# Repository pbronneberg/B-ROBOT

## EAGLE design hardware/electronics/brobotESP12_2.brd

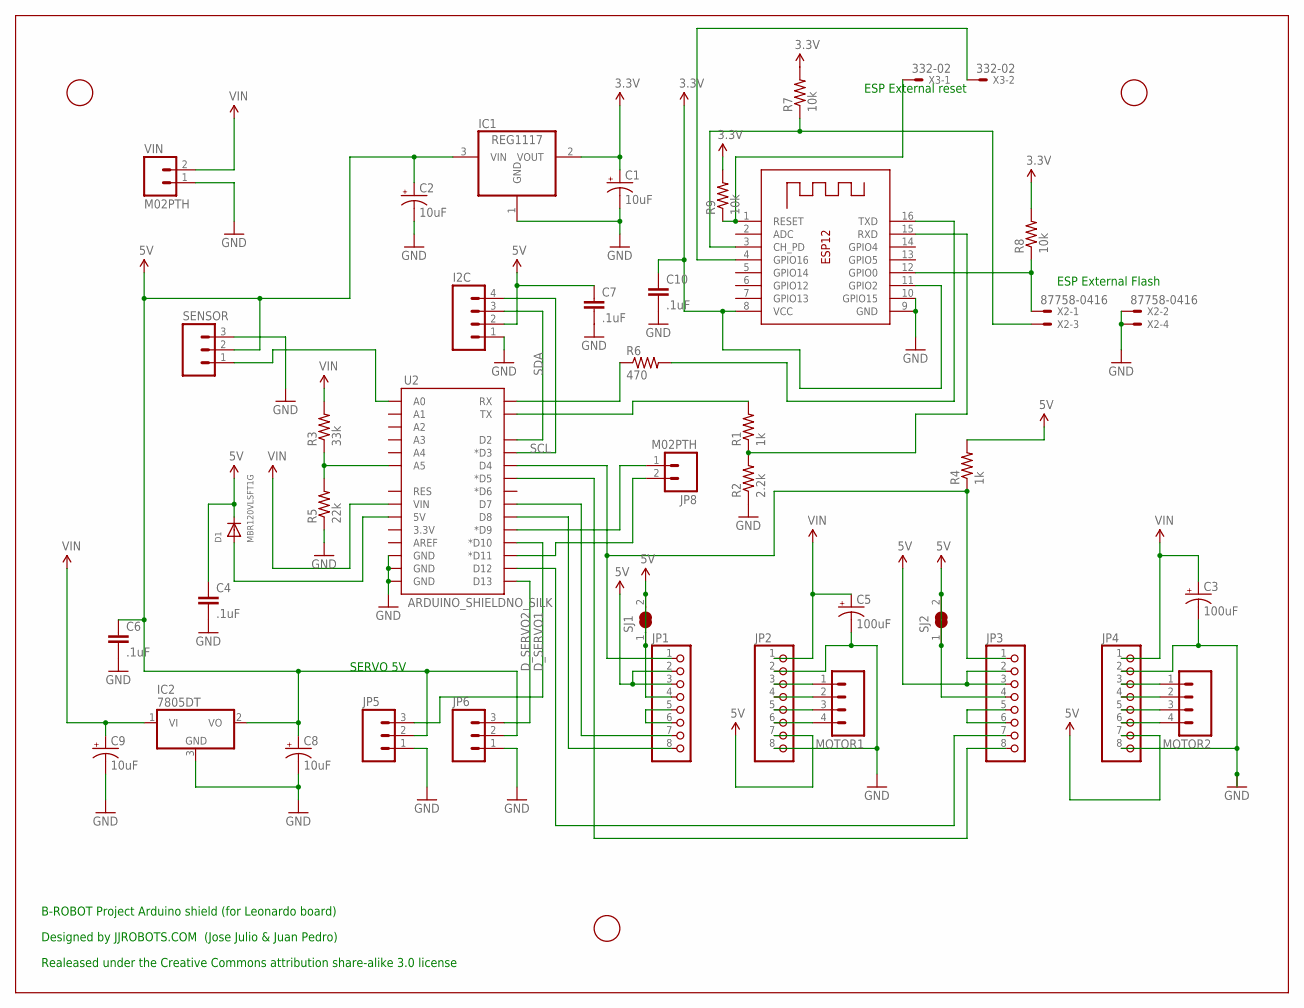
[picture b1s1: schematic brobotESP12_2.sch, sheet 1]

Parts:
C1, C2, C8, C9: 10uF; EIA3216
C3, C5: 100uF; PANASONIC_D
C4, C6, C7, C10: .1uF; 0402-CAP
D1: MBR120VLSFT1G; SOD-123
I2C: M04PTH; 1X04
IC1: REG1117; SOT223
IC2: 7805DT; TO252
JP1, JP2, JP3, JP4: PINHD-1X8; 1X08
JP5, JP6: M03PTH; 1X03
JP8: M02PTH; 1X02
MOTOR1, MOTOR2: M04PTH; 1X04
R1, R4: 1k; 0805
R2: 2.2k; 0805
R3: 33k; 0805
R5: 22k; 0805
R6: 470; 0805
R7, R8, R9: 10k; 0805
SENSOR: M03PTH; 1X03
SJ1, SJ2: SJW
U2: ARDUINO_SHIELDNO_SILK; DUEMILANOVE_VIAS
U$1, U$2, U$3: FIDUCIAL; FIDUCIAL_1MM
VIN: M02PTH; 1X02
X1: ESP-12
X2: 87758-0416
X3: 332-02

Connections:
3.3V: C1.A (+), C10.1, IC1.2 (VOUT), R7.2, R8.2, R9.2, X1.8 (VCC), X1.11 (GPIO2)
5V: C2.A (+), C4.1, C6.1, C7.1, C8.A (+), D1.C, I2C.2, IC1.3 (VIN), IC2.2 (VO), JP1.2, JP1.3, JP1.4, JP2.7, JP3.2, JP3.3, JP3.4, JP4.7, JP5.2, JP6.2, R4.2, SENSOR.2, SJ1.1, SJ1.2, SJ2.1, SJ2.2; also elsewhere on the board
A_SENSOR: SENSOR.1, U2.A0; also elsewhere on the board
A_VOLTAGE: R3.1, R5.2, U2.A5; also elsewhere on the board
D4: JP1.1, JP3.1, R4.1, U2.D4; also elsewhere on the board
D5: JP3.8, U2.D5 (*D5); also elsewhere on the board
D7: JP1.7, U2.D7; also elsewhere on the board
D8: JP1.8, U2.D8; also elsewhere on the board
D11: JP8.2, U2.D11 (*D11); also elsewhere on the board
D12: JP3.7, U2.D12; also elsewhere on the board
D_SERVO1: JP5.3, U2.D10 (*D10); also elsewhere on the board
D_SERVO2: JP6.3, U2.D13; also elsewhere on the board
GND: C1.C (-), C2.C (-), C3.-, C4.2, C5.-, C6.2, C7.2, C8.C (-), C9.C (-), C10.2, I2C.1, IC1.1 (GND), IC2.3 (GND), JP2.2, JP2.8, JP4.2, JP4.8, JP5.1, JP6.1, R2.1, R5.1, SENSOR.3, U2.GND@0 (GND), U2.GND@1 (GND), U2.GND@2 (GND), VIN.1, X1.9 (GND), X1.10 (GPIO15), X2.2, X2.4; also elsewhere on the board
unnamed: JP2.3, MOTOR1.1
unnamed: JP2.4, MOTOR1.2
unnamed: R6.2, X1.16 (TXD)
unnamed: R1.1, R2.2, X1.15 (RXD)
unnamed: JP2.5, MOTOR1.3
unnamed: JP2.6, MOTOR1.4
unnamed: JP4.3, MOTOR2.1
unnamed: JP4.4, MOTOR2.2
unnamed: JP4.5, MOTOR2.3
unnamed: JP1.5, JP1.6
unnamed: JP3.5, JP3.6
unnamed: JP4.6, MOTOR2.4
unnamed: R7.1, X1.3 (CH_PD), X2.3
unnamed: R8.1, X1.12 (GPIO0), X2.1
unnamed: D1.A, U2.5V
unnamed: JP8.1, U2.D9 (*D9)
unnamed: R9.1, X1.1 (RESET), X3.1
unnamed: X1.4 (GPIO16), X3.2
RX_5V: R6.1, U2.RX; also elsewhere on the board
SCL: I2C.4, U2.D3 (*D3); also elsewhere on the board
SDA: I2C.3, U2.D2; also elsewhere on the board
TX_5V: R1.2, U2.TX; also elsewhere on the board
VIN: C3.+, C5.+, C9.A (+), IC2.1 (VI), JP2.1, JP4.1, R3.2, U2.VIN, VIN.2; also elsewhere on the board

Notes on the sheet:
SERVO 5V
B-ROBOT Project Arduino shield (for Leonardo board)
Designed by JJROBOTS.COM (Jose Julio & Juan Pedro)
Realeased under the Creative Commons attribution share-alike 3.0 license
ESP External reset
ESP External Flash

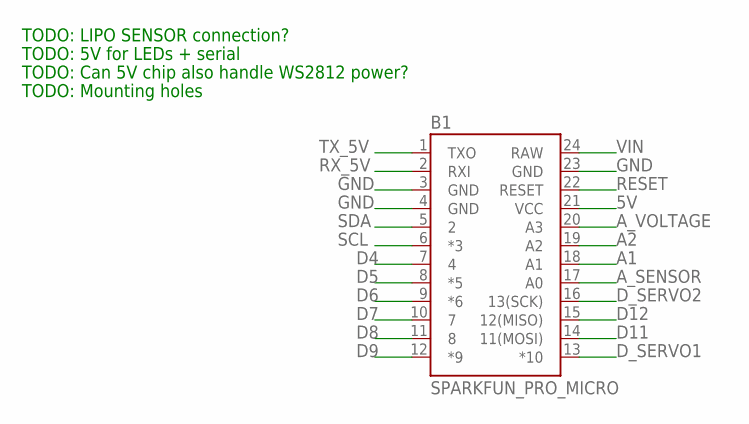
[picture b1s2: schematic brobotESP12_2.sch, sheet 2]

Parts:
B1: SPARKFUN_PRO_MICRO

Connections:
5V: B1.21 (VCC); also elsewhere on the board
A1: B1.18 (A1)
A2: B1.19 (A2)
A_SENSOR: B1.17 (A0); also elsewhere on the board
A_VOLTAGE: B1.20 (A3); also elsewhere on the board
D4: B1.7 (4); also elsewhere on the board
D5: B1.8 (*5); also elsewhere on the board
D6: B1.9 (*6)
D7: B1.10 (7); also elsewhere on the board
D8: B1.11 (8); also elsewhere on the board
D9: B1.12 (*9)
D11: B1.14 (11(MOSI)); also elsewhere on the board
D12: B1.15 (12(MISO)); also elsewhere on the board
D_SERVO1: B1.13 (*10); also elsewhere on the board
D_SERVO2: B1.16 (13(SCK)); also elsewhere on the board
GND: B1.3 (GND), B1.4 (GND), B1.23 (GND); also elsewhere on the board
RESET: B1.22 (RESET)
RX_5V: B1.2 (RXI); also elsewhere on the board
SCL: B1.6 (*3); also elsewhere on the board
SDA: B1.5 (2); also elsewhere on the board
TX_5V: B1.1 (TXO); also elsewhere on the board
VIN: B1.24 (RAW); also elsewhere on the board

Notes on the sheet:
TODO: LIPO SENSOR connection?
TODO: 5V for LEDs + serial
TODO: Can 5V chip also handle WS2812 power?
TODO: Mounting holes

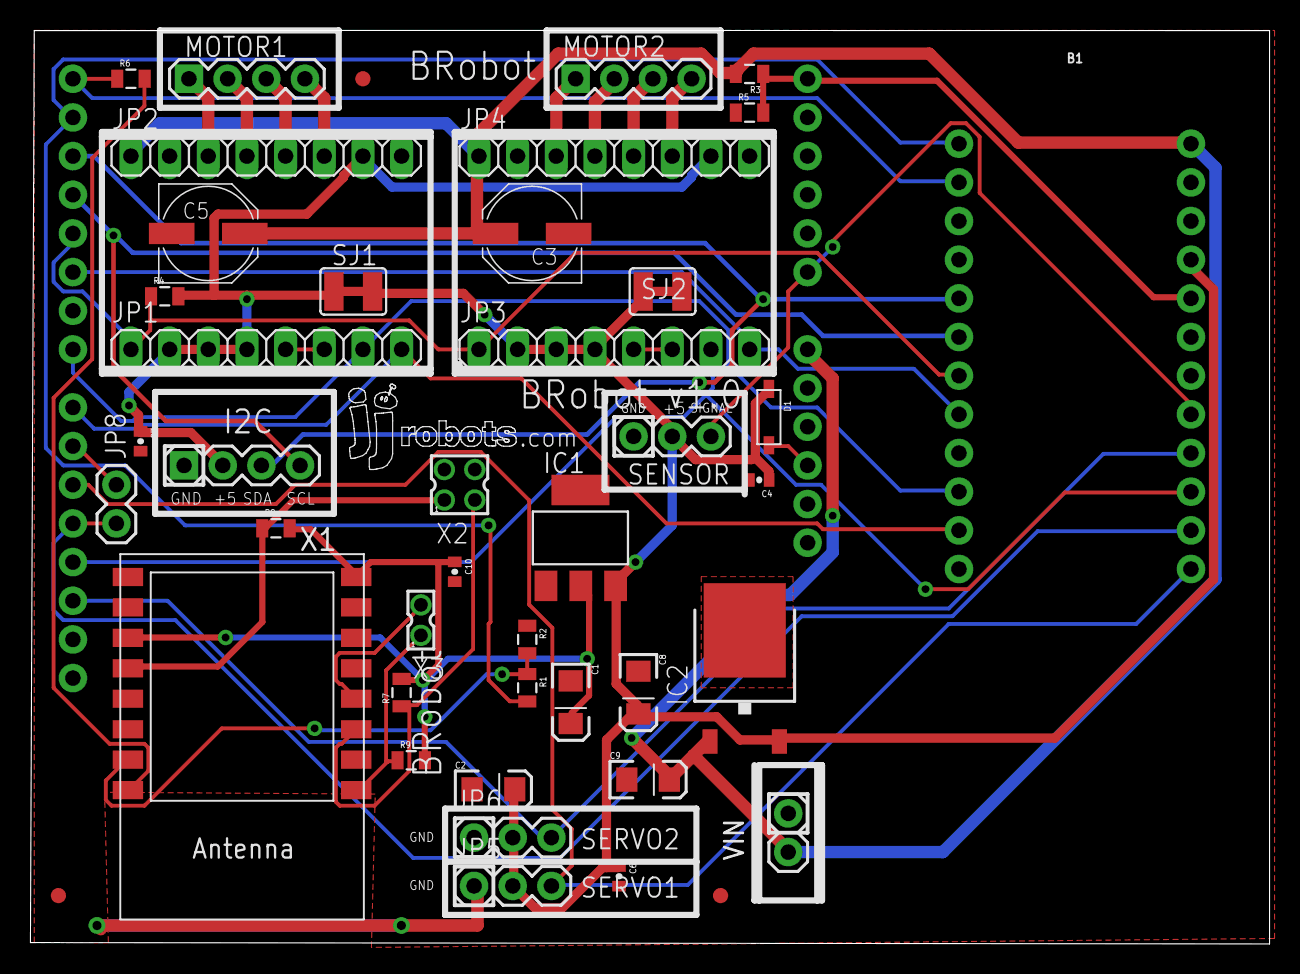
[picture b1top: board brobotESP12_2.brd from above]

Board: 2 copper layers, 81.4 x 60.0 mm, 44 parts (0 on the bottom side), 36 nets.

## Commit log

2017-05-21 added updated board and 3d models
2017-05-22 Added arduino pro micro to the board. Early version, not functional, many todos

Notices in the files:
parts and their libraries:
SparkFun-Boards: Licensing: Creative Commons ShareAlike 4.0 International - https://creativecommons.org/licenses/by-sa/4.0
